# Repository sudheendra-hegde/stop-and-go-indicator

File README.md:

# stop-and-go-indicator

This project is for giving the stop signal to a vehicle entering a narrow road (or bridge etc.) when another vehicle is moving from the other direction. 
<br>The project is based on PIC16F505 microcontroller and uses GY-273 (HMC5883L magnetometer) for the detection of vehicle.
This can be connected to other similar modules through the connector provided on the PCB and hence can be used for more complex application (for example where multiple entrance and exits are there). The connector includes power supply lines and an input (inout) line which can be used to send data between modules asynchronously. Another connector supplies 12V output to the external LED (indicator). ICSP(TM) can be used to dump teh program without removing the microcontroller. Microchip's PIC programmer and software(MPLAB) can be used to program the device. A 12V barrel jack is given for the power supply. 
<br>The pcb has a reverse voltage protection circuit and Transient Voltage Suppressor. The component list can be seen in the Bill Of Materials.

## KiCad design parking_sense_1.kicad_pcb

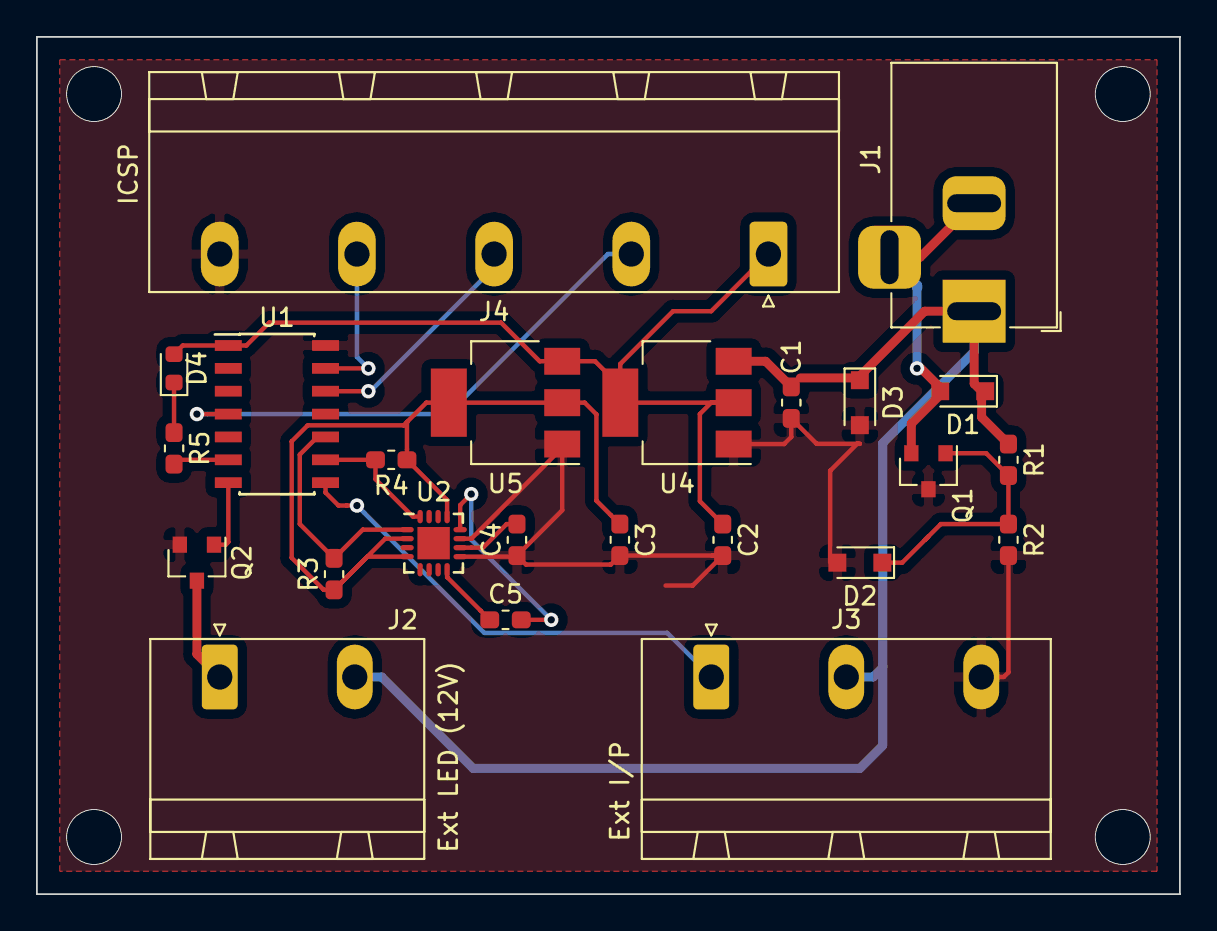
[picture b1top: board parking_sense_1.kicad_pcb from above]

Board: 2 copper layers, 63.5 x 47.6 mm, 24 parts (0 on the bottom side), 19 nets.

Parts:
C1, C2, C3: 22uF; C_0603_1608Metric_Pad1.05x0.95mm_HandSolder
C4: 4.7uF; C_0603_1608Metric_Pad1.05x0.95mm_HandSolder
C5: 0.22uF; C_0603_1608Metric_Pad1.05x0.95mm_HandSolder
D1: D_TVS; D_SOD-323_HandSoldering
D2: GDZ5V1B; D_SOD-323_HandSoldering
D3: D_Schottky_SD0603S020S0R3; D_SOD-323_HandSoldering
D4: LED; D_0603_1608Metric
J1: Barrel_Jack_Switch; BarrelJack_Horizontal
J2: Ext LED (12V); PhoenixContact_GMSTBA_2,5_2-G_1x02_P7.50mm_Horizontal
J3: Ext I/P; PhoenixContact_GMSTBA_2,5_3-G_1x03_P7.50mm_Horizontal
J4: ICSP; PhoenixContact_GMSTBA_2,5_5-G-7,62_1x05_P7.62mm_Horizontal
Q1, Q2: FDN359BN; SOT-23
R1: 9.1k; R_0603_1608Metric_Pad1.05x0.95mm_HandSolder
R2: 6.8k; R_0603_1608Metric_Pad1.05x0.95mm_HandSolder
R3, R4: 4.7k; R_0603_1608Metric_Pad1.05x0.95mm_HandSolder
R5: 560; R_0603_1608Metric_Pad1.05x0.95mm_HandSolder
U1: PIC16F505-ISL; SOIC-14_3.9x8.7mm_P1.27mm
U2: HMC5883L; QFN-16-1EP_3x3mm_P0.5mm_EP1.8x1.8mm
U4: AMS1117-5.0; SOT-223-3_TabPin2
U5: AMS1117-3.3; SOT-223-3_TabPin2

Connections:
CLK: J4.3, U1.12
DATA: J4.4, U1.13
GND: C1.2, C2.2, C3.2, C4.1, D2.2, D3.2, J3.3, J4.5, Q1.3, Q2.2, R2.2, U1.14, U2.9, U2.11, U4.1, U5.1
GND1: D1.2, J1.2, J1.3, Q1.2
IP: J3.1, U1.8
Ledpin: R5.2, U1.6
unnamed: C4.2, U2.10
unnamed: C5.1, U2.8
unnamed: C5.2, U2.12
unnamed: D2.1, Q1.1, R1.2, R2.1
unnamed: D4.1, R5.1
unnamed: J2.1, Q2.3
OP1: Q2.1, U1.7
SCL: R3.2, U1.10, U2.1
SDA: R4.2, U1.9, U2.16
Vcc: C2.1, D4.2, J4.1, U1.1, U4.2, U5.3
Vdd: C3.1, R3.1, R4.1, U2.2, U2.4, U2.13, U5.2
Vin: C1.1, D1.1, D3.1, J1.1, J2.2, J3.2, R1.1, U4.3
Vpp: J4.2, U1.4
